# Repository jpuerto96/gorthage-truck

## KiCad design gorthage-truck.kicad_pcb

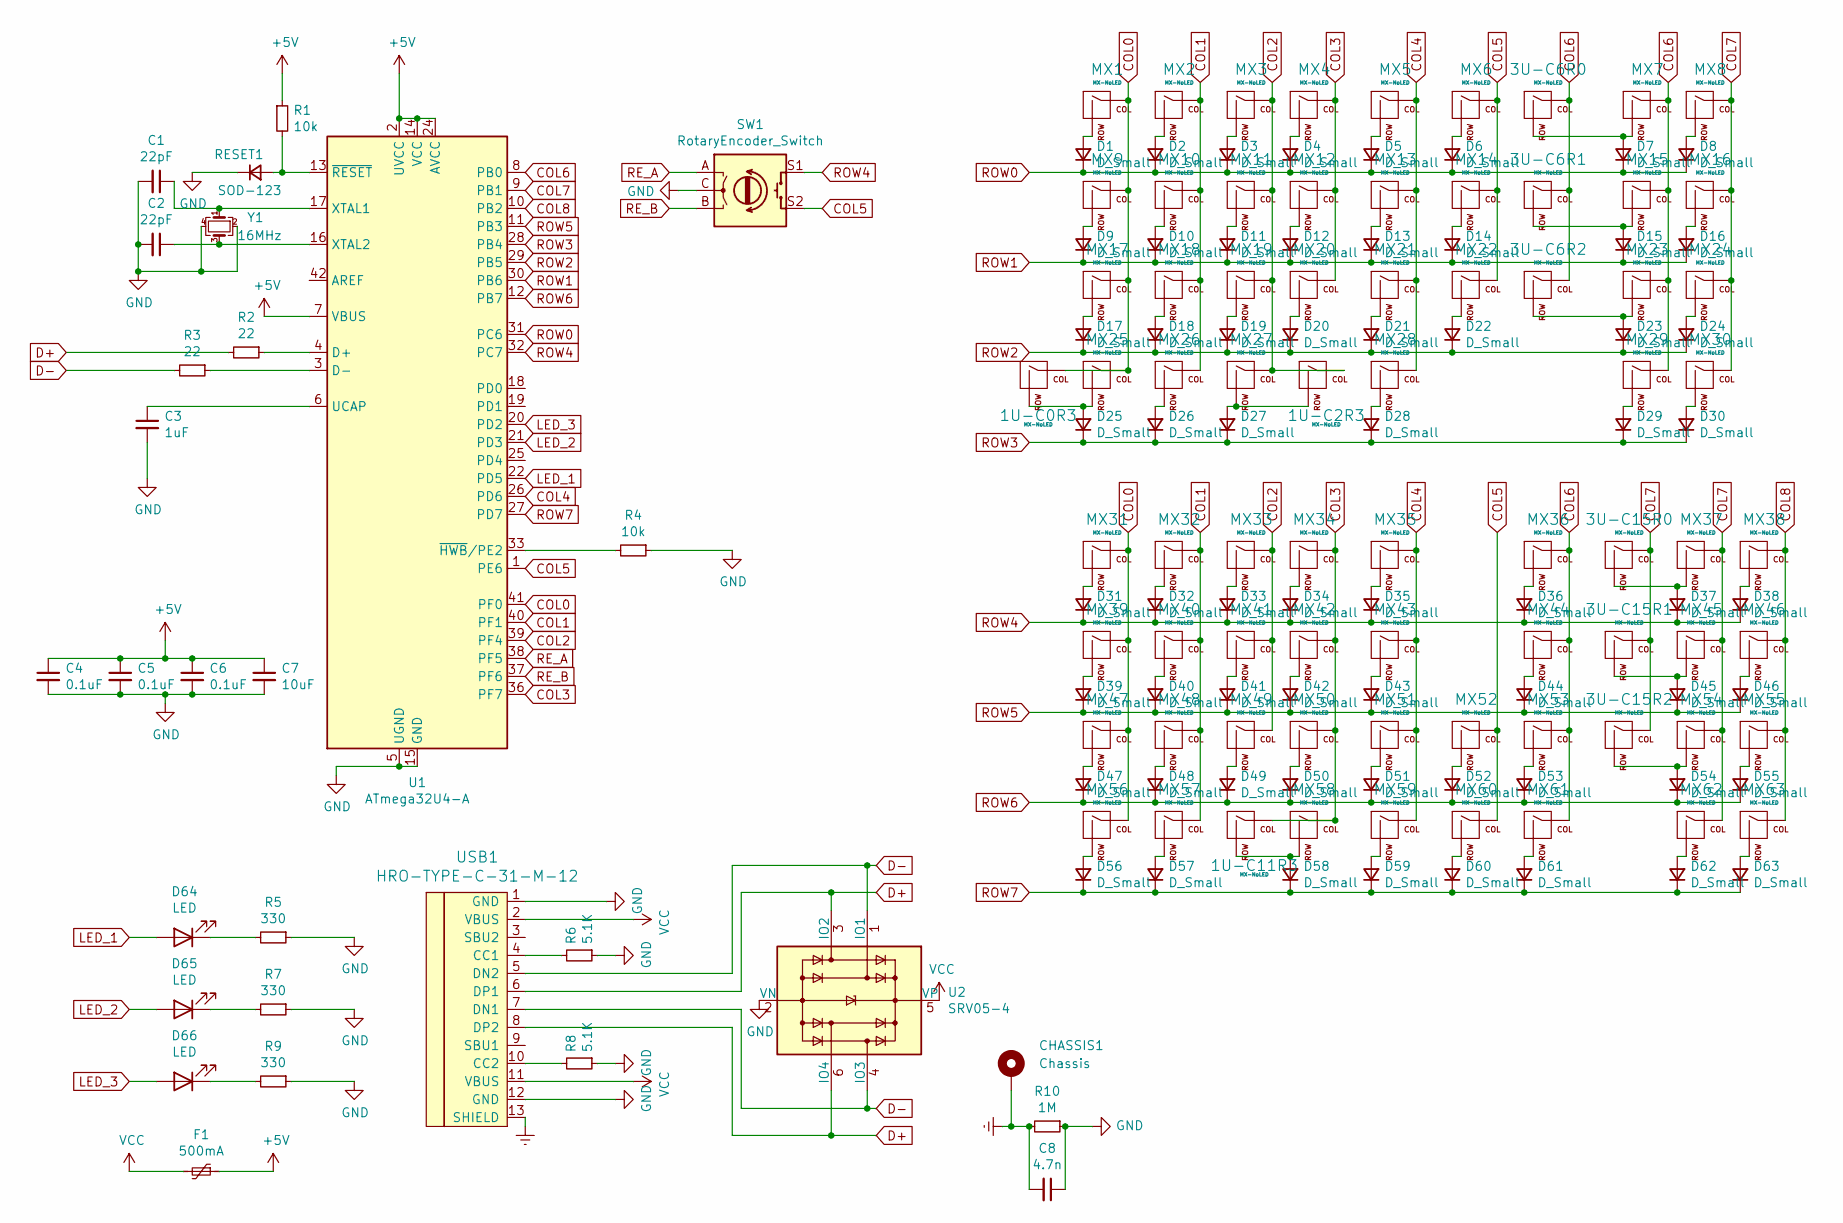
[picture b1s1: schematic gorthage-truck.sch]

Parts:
1U-C0R3, 1U-C2R3, 1U-C11R3: MX-NoLED; MX_1u_NoLED
3U-C6R0, 3U-C6R1, 3U-C6R2, 3U-C15R0, 3U-C15R1, 3U-C15R2: MX-NoLED; MX_3u_NoLED
C1, C2: 22pF; C_0805_2012Metric; LCSC C1804
C3: 1uF; C_0805_2012Metric; LCSC C28323
C4, C5, C6: 0.1uF; C_0805_2012Metric; LCSC C49678
C7: 10uF; C_0805_2012Metric; LCSC C15850
C8: 4.7n; C_0805_2012Metric; LCSC C1744
CHASSIS1: Chassis; TestPoint_Plated_Hole_D2.0mm
D1, D2, D3, D4, D5, D6, D7, D8, D9, D10, D11, D12, D13, D14, D15, D16, D17, D18, D19, D20, D21, D22, D23, D24, D25, D26, D27, D28, D29, D30, D31, D32, D33, D34, D35, D36, D37, D38, D39, D40, D41, D42, D43, D44, D45, D46, D47, D48, D49, D50, D51, D52, D53, D54, D55, D56, D57, D58, D59, D60, D61, D62, D63: D_Small; D_SOD123; LCSC C64898
D64, D65, D66: LED; LED_D3.0mm
F1: 500mA; Fuse_0805_2012Metric; LCSC C261942
MX1, MX2, MX3, MX4, MX5, MX6, MX7, MX8, MX9, MX10, MX11, MX12, MX13, MX14, MX15, MX16, MX17, MX18, MX19, MX20, MX21, MX22, MX23, MX24, MX31, MX32, MX33, MX34, MX35, MX36, MX37, MX38, MX39, MX40, MX41, MX42, MX43, MX44, MX45, MX46, MX47, MX48, MX49, MX50, MX51, MX52, MX53, MX54, MX55, MX59, MX60, MX61, MX62, MX63: MX-NoLED; MX_1u_NoLED
MX25, MX26, MX27, MX57, MX58: MX-NoLED; MX_1.25u_NoLED
MX28, MX56: MX-NoLED; MX_3u_ReversedStabilizers_NoLED
MX29: MX-NoLED; MX-ALPS_10u_ReversedStabilizers_NoLED
MX30: MX-NoLED; MX_7u_ReversedStabilizers_NoLED
R1, R4: 10k; R_0805_2012Metric; LCSC C17414
R2, R3: 22; R_0805_2012Metric; LCSC C17561
R5, R7, R9: 330; R_0805_2012Metric; LCSC C26010
R6, R8: 5.1K; R_0805_2012Metric; LCSC C27834
R10: 1M; R_0805_2012Metric; LCSC C17514
RESET1: SOD-123; D_SOD-123
SW1: RotaryEncoder_Switch; RotaryEncoder_EC11-no-legs
U1: ATmega32U4-A; TQFP-44_10x10mm_P0.8mm; LCSC C44854
U2: SRV05-4; SOT-23-6; LCSC C85364
USB1: HRO-TYPE-C-31-M-12; LCSC C165948
Y1: 16MHz; Crystal_SMD_3225-4Pin_3.2x2.5mm; LCSC C13738

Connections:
+5V: C4.1, C5.1, C6.1, C7.1, F1.1, R1.1, U1.2 (UVCC), U1.7 (VBUS), U1.14 (VCC), U1.24 (AVCC), U1.34 (VCC), U1.44 (AVCC)
COL0: 1U-C0R3.1 (COL), MX1.1 (COL), MX9.1 (COL), MX17.1 (COL), MX25.1 (COL), MX31.1 (COL), MX39.1 (COL), MX47.1 (COL), MX56.1 (COL), U1.41 (PF0)
COL1: MX2.1 (COL), MX10.1 (COL), MX18.1 (COL), MX26.1 (COL), MX32.1 (COL), MX40.1 (COL), MX48.1 (COL), MX57.1 (COL), U1.40 (PF1)
COL2: 1U-C2R3.1 (COL), MX3.1 (COL), MX11.1 (COL), MX19.1 (COL), MX27.1 (COL), MX33.1 (COL), MX41.1 (COL), MX49.1 (COL), U1.39 (PF4)
COL3: 1U-C11R3.1 (COL), MX4.1 (COL), MX12.1 (COL), MX20.1 (COL), MX34.1 (COL), MX42.1 (COL), MX50.1 (COL), MX58.1 (COL), U1.36 (PF7)
COL4: MX5.1 (COL), MX13.1 (COL), MX21.1 (COL), MX28.1 (COL), MX35.1 (COL), MX43.1 (COL), MX51.1 (COL), MX59.1 (COL), U1.26 (PD6)
COL5: MX6.1 (COL), MX14.1 (COL), MX22.1 (COL), MX52.1 (COL), MX60.1 (COL), SW1.S2, U1.1 (PE6)
COL6: 3U-C6R0.1 (COL), 3U-C6R1.1 (COL), 3U-C6R2.1 (COL), MX7.1 (COL), MX15.1 (COL), MX23.1 (COL), MX29.1 (COL), MX36.1 (COL), MX44.1 (COL), MX53.1 (COL), MX61.1 (COL), U1.8 (PB0)
COL7: 3U-C15R0.1 (COL), 3U-C15R1.1 (COL), 3U-C15R2.1 (COL), MX8.1 (COL), MX16.1 (COL), MX24.1 (COL), MX30.1 (COL), MX37.1 (COL), MX45.1 (COL), MX54.1 (COL), MX62.1 (COL), U1.9 (PB1)
COL8: MX38.1 (COL), MX46.1 (COL), MX55.1 (COL), MX63.1 (COL), U1.10 (PB2)
D+: R2.2, U2.3 (IO2), U2.6 (IO4), USB1.6 (DP1), USB1.8 (DP2)
D-: R3.2, U2.1 (IO1), U2.4 (IO3), USB1.5 (DN2), USB1.7 (DN1)
Earth: C8.2, CHASSIS1.1, R10.2, USB1.13 (SHIELD)
GND: C1.2, C2.2, C3.2, C4.2, C5.2, C6.2, C7.2, C8.1, R4.1, R5.1, R6.1, R7.1, R8.1, R9.1, R10.1, RESET1.1 (K), SW1.C, U1.5 (UGND), U1.15 (GND), U1.23 (GND), U1.35 (GND), U1.43 (GND), U2.2 (VN), USB1.1 (GND), USB1.12 (GND), Y1.2, Y1.4
LED_1: D64.2 (A), U1.22 (PD5)
LED_2: D65.2 (A), U1.21 (PD3)
LED_3: D66.2 (A), U1.20 (PD2)
unnamed: 1U-C0R3.2 (ROW), D25.2 (A), MX25.2 (ROW)
unnamed: 1U-C2R3.2 (ROW), D27.2 (A), MX27.2 (ROW)
unnamed: 1U-C11R3.2 (ROW), D58.2 (A), MX58.2 (ROW)
unnamed: 3U-C6R0.2 (ROW), D7.2 (A), MX7.2 (ROW)
unnamed: 3U-C6R1.2 (ROW), D15.2 (A), MX15.2 (ROW)
unnamed: 3U-C6R2.2 (ROW), D23.2 (A), MX23.2 (ROW)
unnamed: 3U-C15R0.2 (ROW), D37.2 (A), MX37.2 (ROW)
unnamed: 3U-C15R1.2 (ROW), D45.2 (A), MX45.2 (ROW)
unnamed: 3U-C15R2.2 (ROW), D54.2 (A), MX54.2 (ROW)
unnamed: C1.1, U1.17 (XTAL1), Y1.1
unnamed: C2.1, U1.16 (XTAL2), Y1.3
unnamed: C3.1, U1.6 (UCAP)
unnamed: D1.2 (A), MX1.2 (ROW)
unnamed: D2.2 (A), MX2.2 (ROW)
unnamed: D3.2 (A), MX3.2 (ROW)
unnamed: D4.2 (A), MX4.2 (ROW)
unnamed: D5.2 (A), MX5.2 (ROW)
unnamed: D6.2 (A), MX6.2 (ROW)
unnamed: D8.2 (A), MX8.2 (ROW)
unnamed: D9.2 (A), MX9.2 (ROW)
unnamed: D10.2 (A), MX10.2 (ROW)
unnamed: D11.2 (A), MX11.2 (ROW)
unnamed: D12.2 (A), MX12.2 (ROW)
unnamed: D13.2 (A), MX13.2 (ROW)
unnamed: D14.2 (A), MX14.2 (ROW)
unnamed: D16.2 (A), MX16.2 (ROW)
unnamed: D17.2 (A), MX17.2 (ROW)
unnamed: D18.2 (A), MX18.2 (ROW)
unnamed: D19.2 (A), MX19.2 (ROW)
unnamed: D20.2 (A), MX20.2 (ROW)
unnamed: D21.2 (A), MX21.2 (ROW)
unnamed: D22.2 (A), MX22.2 (ROW)
unnamed: D24.2 (A), MX24.2 (ROW)
unnamed: D26.2 (A), MX26.2 (ROW)
unnamed: D28.2 (A), MX28.2 (ROW)
unnamed: D29.2 (A), MX29.2 (ROW)
unnamed: D30.2 (A), MX30.2 (ROW)
unnamed: D31.2 (A), MX31.2 (ROW)
unnamed: D32.2 (A), MX32.2 (ROW)
unnamed: D33.2 (A), MX33.2 (ROW)
unnamed: D34.2 (A), MX34.2 (ROW)
unnamed: D35.2 (A), MX35.2 (ROW)
unnamed: D36.2 (A), MX36.2 (ROW)
unnamed: D38.2 (A), MX38.2 (ROW)
unnamed: D39.2 (A), MX39.2 (ROW)
unnamed: D40.2 (A), MX40.2 (ROW)
unnamed: D41.2 (A), MX41.2 (ROW)
unnamed: D42.2 (A), MX42.2 (ROW)
unnamed: D43.2 (A), MX43.2 (ROW)
unnamed: D44.2 (A), MX44.2 (ROW)
unnamed: D46.2 (A), MX46.2 (ROW)
unnamed: D47.2 (A), MX47.2 (ROW)
unnamed: D48.2 (A), MX48.2 (ROW)
unnamed: D49.2 (A), MX49.2 (ROW)
unnamed: D50.2 (A), MX50.2 (ROW)
unnamed: D51.2 (A), MX51.2 (ROW)
unnamed: D52.2 (A), MX52.2 (ROW)
unnamed: D53.2 (A), MX53.2 (ROW)
unnamed: D55.2 (A), MX55.2 (ROW)
unnamed: D56.2 (A), MX56.2 (ROW)
unnamed: D57.2 (A), MX57.2 (ROW)
unnamed: D59.2 (A), MX59.2 (ROW)
unnamed: D60.2 (A), MX60.2 (ROW)
unnamed: D61.2 (A), MX61.2 (ROW)
unnamed: D62.2 (A), MX62.2 (ROW)
unnamed: D63.2 (A), MX63.2 (ROW)
unnamed: D64.1 (K), R5.2
unnamed: D65.1 (K), R7.2
unnamed: D66.1 (K), R9.2
unnamed: R1.2, RESET1.2 (A), U1.13 (~RESET)
unnamed: R2.1, U1.4 (D+)
unnamed: R3.1, U1.3 (D-)
unnamed: R4.2, U1.33 (~HWB~/PE2)
unnamed: R6.2, USB1.4 (CC1)
unnamed: R8.2, USB1.10 (CC2)
RE_A: SW1.A, U1.38 (PF5)
RE_B: SW1.B, U1.37 (PF6)
ROW0: D1.1 (K), D2.1 (K), D3.1 (K), D4.1 (K), D5.1 (K), D6.1 (K), D7.1 (K), D8.1 (K), U1.31 (PC6)
ROW1: D9.1 (K), D10.1 (K), D11.1 (K), D12.1 (K), D13.1 (K), D14.1 (K), D15.1 (K), D16.1 (K), U1.30 (PB6)
ROW2: D17.1 (K), D18.1 (K), D19.1 (K), D20.1 (K), D21.1 (K), D22.1 (K), D23.1 (K), D24.1 (K), U1.29 (PB5)
ROW3: D25.1 (K), D26.1 (K), D27.1 (K), D28.1 (K), D29.1 (K), D30.1 (K), U1.28 (PB4)
ROW4: D31.1 (K), D32.1 (K), D33.1 (K), D34.1 (K), D35.1 (K), D36.1 (K), D37.1 (K), D38.1 (K), SW1.S1, U1.32 (PC7)
ROW5: D39.1 (K), D40.1 (K), D41.1 (K), D42.1 (K), D43.1 (K), D44.1 (K), D45.1 (K), D46.1 (K), U1.11 (PB3)
ROW6: D47.1 (K), D48.1 (K), D49.1 (K), D50.1 (K), D51.1 (K), D52.1 (K), D53.1 (K), D54.1 (K), D55.1 (K), U1.12 (PB7)
ROW7: D56.1 (K), D57.1 (K), D58.1 (K), D59.1 (K), D60.1 (K), D61.1 (K), D62.1 (K), D63.1 (K), U1.27 (PD7)
VCC: F1.2, U2.5 (VP), USB1.2 (VBUS), USB1.11 (VBUS)

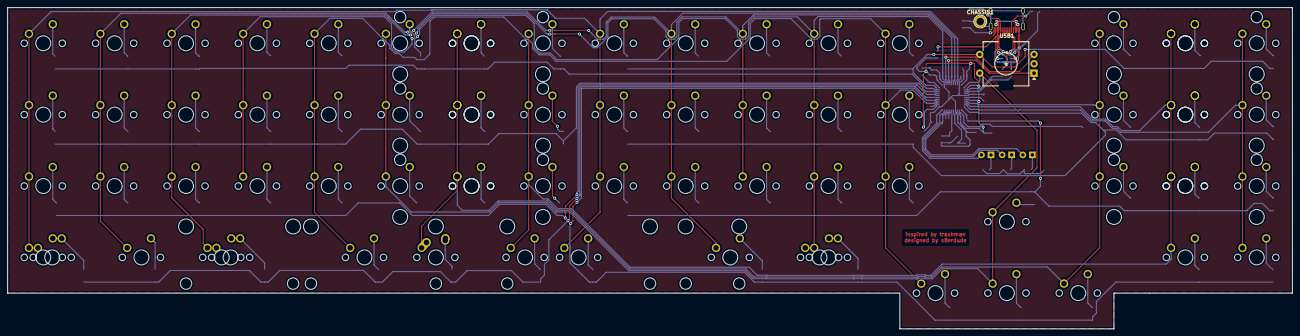
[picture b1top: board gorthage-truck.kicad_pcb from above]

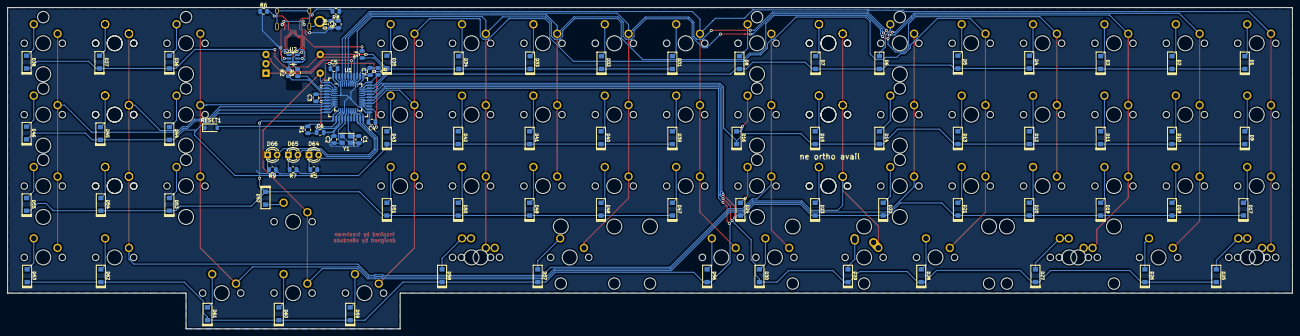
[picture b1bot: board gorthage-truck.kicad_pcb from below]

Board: 2 copper layers, 342.9 x 85.7 mm, 164 parts (89 on the bottom side), 103 nets.

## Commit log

2021-04-08 Init gorthage truck
2021-04-22 v1 pending silk
2023-05-23 Add gitignore
2023-05-23 Release Files
